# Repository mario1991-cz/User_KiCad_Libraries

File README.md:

# User KiCad Libraries

Personal KiCad 10 libraries (symbols, footprints, 3D models, SPICE models, design blocks).
Kept outside projects; all library-table entries use the path variable `${USER_LIB_DIR}`,
so the folder can be moved by changing that one variable. Kept in a Git repository (GitHub).

## Layout
| Folder | Content | Naming |
|---|---|---|
| `symbols/` | `.kicad_sym` libraries | `User_<Category>.kicad_sym` |
| `footprints/` | `.pretty` libraries | `User_<Category>.pretty` |
| `3dmodels/` | `.3dshapes` folders, STEP only | `User_<Category>.3dshapes` (same category as the footprint library) |
| `spice/` | SPICE models (`.lib`, `.mod`, `.sub`) | manufacturer or part family name |
| `design_blocks/` | `.kicad_blocks` libraries | `User_<Category>.kicad_blocks` |

Categories follow the official KiCad library names (`Regulator_Switching`, `Amplifier_Operational`,
`Connector`, `74xx`, ...). A library is created when its first part is added, never empty.

## Rules
- Use an official KiCad symbol/footprint whenever one exists. Add a part here only if KiCad lacks it
  or it needs a deliberate deviation.
- Prefer KiCad's official footprints in own symbols; own footprints only when KiCad has none.
- Symbols follow KiCad KLC style: 2.54 mm pin grid, inputs left, outputs right, power top/bottom,
  IEC (European) graphic conventions.
- Mandatory symbol fields: Reference, Value, Footprint, Datasheet (manufacturer PDF URL),
  Description, Keywords (`ki_keywords`), Footprint filters (`ki_fp_filters`).
- `Sim.*` fields (Sim.Library, Sim.Name, Sim.Device, Sim.Pins) are filled whenever a SPICE model is
  available; `Sim.Library` uses `${USER_LIB_DIR}/spice/<file>`. Models need ngspice with XSPICE
  (KiCad's ngspice has it).
- Models whose licence forbids redistribution (e.g. Central Semiconductor 2N5551) are not stored here:
  the symbol uses `Sim.Library = ${KIPRJMOD}/spice/<file>` and each project keeps its own copy of the model.
- Every new model is checked in ngspice before it is linked; LTspice-only syntax (`mfg=`, `Vceo=`, `Icrating=`,
  Diotec-style parametrised subcircuits) makes ngspice abort.
- No Manufacturer / MPN fields; vendor/SnapEDA extra fields (MF, MP, Price, Availability, PARTREV, ...) are removed.
- Names of own parts stay short and readable (original vendor names), KiCad naming conventions are not enforced.
- Connector pins are `passive` (power source pins only on real sources such as regulator/converter outputs).
- References in designs always end with a number (KiCad refuses to simulate `Rz` etc.).
- All texts, names and comments in English.

## User_74xx_CSN and User_4xxx_CSN – unofficial, obsolete symbol style
> **Warning:** `User_74xx_CSN` and `User_4xxx_CSN` are **unofficial** libraries. Its symbols follow the classic Czechoslovak
> ČSN drawing style known from TESLA catalogues. That standard is **withdrawn** and has been replaced by
> ČSN EN 60617-12 (IEC 60617-12). The library is kept for hobby and retro (TESLA) projects only; do not use it
> where conformity with current standards is required.
- Simple gates look the same in both standards (rectangle with `&`, `≥1`, `1`, `=1`, negation circle).
- Flip-flops, counters, decoders etc. are drawn in the classic style (TESLA catalogue), not with IEC dependency notation.
- One unit per gate/element plus a separate power unit (VCC/GND); Footprint field left empty, footprint filters for DIP/SOIC/TSSOP.
- Keywords contain the TESLA equivalent (e.g. `MH7400`) for searching.
- Layout of complex parts: three columns (input labels | function abbreviation | output labels); groups separated by
  lines, group headers such as `&G`, `&L`, `A`, `Z` (3-state outputs). Abbreviations as in TESLA catalogues:
  `T` flip-flop, `TE` edge register, `TL`/`RGL` latch, `RG8` shift register, `CT2`/`CT10` counter,
  `B/D`, `B/DEC`, `DC`, `X/Y` decoders, `MUX`/`MX` multiplexer, `SM` adder.
- Clock inputs: filled arrow. Tip at the body = rising edge (`C_H`); tip pointing away from the body
  towards the pin = falling edge (`C_L`, e.g. 74112). Negation = circle.
- Parts without a TESLA catalogue drawing (e.g. 74161, 74163, 74191, 74165, 74595) are drawn from their function in the same style.
- Generated by local scripts (not in the repository).
- 4000 series: supply pins VDD/VSS (4051/4052/4053 also VEE in the power unit); analog switch/multiplexer channels are `passive` pins; keywords contain the TESLA name (e.g. `MHB4011`).

## Design blocks
- A block contains only footprints, tracks and vias (plus the schematic). **No zones/copper pours and no Edge.Cuts outline**:
  pours are a board-level decision and the target board's planes connect the nets.
- Every GND pad gets its own short trace + via, so GND connects to the target board's plane on any layer
  (a 2-layer target without any GND pour would show these vias as unconnected in DRC).
- Pours and a temporary outline may be used in the block's work project only, to verify connectivity with DRC.
- A block has no required shape; in KiCad it is just a group.
- Usage in the PCB editor: **place the design block first, then run "Update PCB from Schematic"**.
  Updating first brings the block's parts in as loose footprints without the layout.
- Placed blocks are not updated when the library block changes.

## Tools
Helper scripts (3D model generators, symbol generators, mechanical drawing) are kept locally in `tools/`
and are deliberately **not part of this repository** (`.gitignore`). Models and symbols made with them are
ordinary KiCad/STEP files and need no script.

## Candidates (add when needed)
- 4000 series: 4020, 4024 (binary counters), 4026, 4033 (decade counter + 7-segment decoder), 4510, 4516 (up/down counters),
  4514, 4515 (1-of-16 decoder with latch), 4067 (16-channel analog mux), 4099 (8-bit addressable latch; TESLA drawing exists),
  4042 (quad D latch), 4543 (BCD to 7-segment LCD decoder), 4098 (dual monostable).
- 74HC40xx parts (74HC4051/4052/4053/4060/4040/4017 …) are pin-compatible with the 4000 originals: use the User_4xxx_CSN
  symbol and change Value (mind the 2–6 V supply range of HC).

## Contents
| Library | Part | Notes |
|---|---|---|
| `User_Regulator_Switching` (symbol) | TPS5405DR | TI 6.5–28 V in, 5 V fixed out, 2 A buck, SOIC-8, uses KiCad footprint `Package_SO:SOIC-8_3.9x4.9mm_P1.27mm`. No SPICE model from TI. |
| `User_Power` (design block) | TPS5405_5V_2A | Proven 5 V / 2 A supply from project PNAE (schematic) with a new 2-layer PCB layout (DRC clean). GND zones removed 2026-10-24 – only footprints, tracks and per-pad GND vias. |
| `User_Connector` (symbol + footprint + 3D) | RASPBERRYPI_B+_IDC / AMPHENOL_75869-107LF | Raspberry Pi 40-pin GPIO header with signal names (Adafruit symbol), shrouded 2x20 box header; pad 1 square. |
| `User_Connector` (symbol + footprint + 3D) | PJ-047A / CUI_PJ-047A | Same Sky (CUI) DC jack, 2.0 mm pin, 2.5 A, THT; all pins passive, shield pins unified as SHIELD. |
| `User_Connector` (symbol + footprint + 3D) | RCJ-04x / CUI_RCJ-04x | Same Sky (CUI) RCJ-04x RCA jack, right angle, THT (x = housing colour, 1 black ... 7 orange); pin 2 = centre (signal), pin 1 = sleeve (GND). Board-edge part: front face of the body at x = -4 mm = board edge; the two locating notches (1.7 × 1.8 mm, open to the edge) are drawn on Edge.Cuts inside the footprint and are milled with the outline (join the board outline to their end points). 3D model Same_Sky_RCJ-041.step (rotation/offset to be checked in the 3D viewer). |
| `User_Connector` | HTST-117-01-L-DV-A | Samtec shrouded header 2×17, 2.54 mm, SMD vertical, alignment pins (-A). Symbol = KiCad `Connector_Generic:Conn_02x17_Odd_Even` with fields filled, ref J, passive pins. Footprint `SAMTEC_HTST-117-01-L-DV-A` per Samtec HTST-SM rev D: pads 1.27 × 5.08 mm at ±3.43 mm, 2× NPTH Ø1.676 at ±19.05 mm, origin = connector centre, pin 1 bottom left (odd row at +Y), as `AMPHENOL_75869-107LF`. 3D = Samtec/TraceParts STEP rotated into KiCad axes by rewriting its points/directions (X→−X, Z→Y, Y+1.27→Z), so the footprint needs no rotation/offset. |
| `User_Converter_DCDC` (symbol + footprint + 3D) | TMR 9-2423WI / CONV_TMR_9-2423 | TRACO 9 W isolated DC/DC, 9-36 V in, +/-15 V 300 mA, SIP-8; pinout and footprint checked against the TMR 9WI datasheet. |
| `User_Transistor_FET` (symbol) | BUZ71 | 50 V / 14 A / 0.1 Ω N-channel MOSFET, TO-220 (pins 1 G, 2 D, 3 S; tab = drain). Graphics copied from KiCad `Transistor_FET:BUZ11`, footprint `Package_TO_SOT_THT:TO-220-3_Vertical`. |
| `User_Display_Character` (symbols) + `User_Display_7Segment` (footprint + 3D) | SA08-11GWA, SA08-11EWA, SA08-11SRWA, SA08-11YWA / SA08-11xxx | Kingbright 20.32 mm (0.8") single-digit 7-segment display, common anode, right-hand decimal. Colour variants are derived symbols of SA08-11GWA (graphics from KiCad `Display_Character:SA15-11SRWA`); pins A1 B14 C12 D10 E4 F2 G13 DP9, CA 3/5/11/16 (all four shown), pin 6 = hidden NC (no chip); pins 7, 8, 15 do not exist. Footprint `SA08-11xxx`: 13 pads 1.6 mm / drill 0.8 mm for the 0.5 mm pins (hand soldering; the datasheet's 1.0 mm lets too much solder through), pad 1 square. 3D model generated by a local script (the public model has 16 pins, no colours and 2.6 MB). Datasheet: keep the body ≥ 5 mm from the board edge for wave soldering. |
| `User_Mechanical` (symbol) + `User_Heatsink` (footprint + 3D) | V4330N | Assmann WSW V4330N heatsink for a TO-220 lying between the fins (29 × 20 × 11.5 mm, 12 K/W). Separate mechanical part (ref HS, graphics from KiCad `Mechanical:Heatsink`), footprint without pads, **origin = centre of the M3 hole** – drag it onto the transistor's hole, KiCad snaps it. The hole itself belongs to the transistor footprint. STEP = TraceParts model moved so the hole is at the origin. |
| `User_Heatsink` (footprint + 3D) | V4330N_Vertical | Alternative upright mounting of the V4330N (stands on its 29 × 11.5 mm end, 20 mm high): TO-220 tab on the inner face of the base between the fins; 2× NPTH Ø3.0 for self-tapping screws into the profile grooves, pitch 24 mm, 1.25 mm behind the lead axis. **Origin = pin 1 of the transistor** – drag it onto pad 1, KiCad snaps it. STEP = the V4330N model rotated upright in the file (hole 17 mm above the board). |
| `User_Package_TO_SOT_THT` (footprint) | TO-220-3_Vertical_A2.5mm_Z1mm, TO-220-2_Vertical_A2.5mm_Z1mm | KiCad TO-220 vertical footprints for V4330N_Vertical: pads unchanged, graphics with the tab back 2.5 mm behind the lead axis (datasheet A2 ≈ 2.5 mm; KiCad uses 3.15), KiCad 3D model with offset (0, −0.65, 1) so the tab sits on the heatsink and its hole is 17 mm above the board. |
| `User_Package_TO_SOT_THT` (footprint + 3D) | TO-220-3_Horizontal_TabDown_L20.32mm_Z2.5mm | TO-220 lying tab down on a heatsink base 2.5 mm above the board, leads bent 20.32 mm from the M3 hole (Ø3.2) axis; pads 1.905 × 2 / drill 1.1, origin pin 1. For V4330N and other heatsinks mounted the same way. |
| `User_Heatsink` (footprint + 3D) | HSS-B20-061H-03 | Same Sky (CUI) stamped TO-220 clip heatsink 19 × 12.7 × 13 mm with one solder pin (oval PTH; unused if a heatsink without pin is fitted). Geometry copied from KiCad `Heatsink:Heatsink_AAVID_576802B03900G` (practically identical), 3D model from Same Sky (`HSS-B20-061H-03.step`, rotation tuned by the user in Electronic_load). Use with symbol `Mechanical:Heatsink_Pad` or as a board-only footprint. |
| `User_Diode` (symbol) + `User_Diode_THT` (footprint + 3D) | SBX3040-3G | Diotec 40 V / 30 A Schottky rectifier, axial Ø8 × 7.5 mm (~P600, "D8x7.5_LowRth"), leads Ø1.6 mm. Symbol graphics from KiCad `Device:D_Schottky` (pin 1 K, 2 A). Footprint `SBX3040-3G`: horizontal, pitch 17.78 mm, pads 3.4 mm, drill 1.9 mm (production-proven; 1.8 mm soldered badly), pad 1 = K square. 3D model generated by a local script (bent leads, bend radius 1.6 mm). No SPICE model from Diotec. |
| `User_Potentiometer_THT` (footprint + 3D) | CA9PV10 | ACP CA9 10 mm trimmer, vertical, pins 2.5 × 5 mm apart. Geometry from KiCad `Potentiometer_THT:Potentiometer_ACP_CA9-V10_Vertical`, whose 3D model does not exist in KiCad. 3D model `CA9PV10.stp` from ACP, offset (17.99, -23.948, 5.8), rotate (0, 0, 90): checked in a KiCad STEP export, pins on pads and shoulder on the board. Height 6.1 mm above the board. |
| `User_Device` (symbol) | 3862C-162 | Bourns 3862 panel pot: graphics, pins and SPICE fields of KiCad `Device:R_Potentiometer` (1 = end, 2 = wiper, 3 = end), ref **P** (user convention), Value = resistance (default 10k), footprint preset `User_Potentiometer_Panel:3862C-162`, footprint filter `User_Potentiometer_Panel:*` (only panel pots offered). One symbol for all resistance values. |
| `User_Regulator_Switching` (symbol) + `User_Package_DIP` (footprint + 3D) | VIPER37LE / SDIP-10_W7.62mm_P1.778mm | ST VIPerPlus offline converter, 800 V, 60 kHz, SDIP10 (H = 115 kHz variant not added – user uses LE only). Symbol in the style of KiCad `VIPer26LN`: 1 GND, 2 VDD, 3 CONT, 4 FB, 5 BR, 6–10 DRAIN (7–10 stacked, hidden), ref U, footprint preset. Footprint: shrink DIP pitch 1.778 mm (70 mil), rows 7.62 mm, pads 1.78 × 1.27 mm, drill **0.6 mm – proven on the user's ViPer37LE board** (pins 0.36–0.56 mm fit), pad 1 square, origin pin 1, KiCad DIP-style silk/fab/courtyard. Heat-sink copper under DRAIN is drawn on the board (shape depends on the layout). 3D generated by a local script (KiCad has no SDIP10; the old workaround was the DIP-10 model scaled Y 0.7). |
| `User_Mechanical` (symbol) + `User_Heatsink` (footprint + 3D) + `User_Package_TO_SOT_THT` (footprint) | V2012B / TO-126-3_Vertical_Z4.1mm | Assmann WSW V2012B **clip-on** heatsink for TO-126 (black anodized, 22 × 11 × 19 mm, 21 K/W, sheet 0.8 mm), drawing ASS 0862 HS rev02. Separate mechanical part like V4330N: symbol ref HS (no pins), footprint origin = pin 1 of the transistor. The transistor slides **inside**, metal back on the inner face of the flat wall, top edge against the Ø1.5 dimple stop (the Ø3 hole is only for the alternative screw mounting, not used with the clip). Two solder pins, **not connected** (pads without number), in **slots 1.1 × 2.0 mm** (pad 2.2 × 3.1, annular ring 0.55 mm; less solder flowing through when hand soldering) at x −8.32 / 12.88, y +2.175 (pitch 21.2). The 3.2 mm wide pin shoulders keep the heatsink **3 mm above the board**. STEP from Assmann/TraceParts checked against the drawing (all dimensions match), rotated 180° about X in the file (representation frame left at identity) and coloured black. Transistor footprint `TO-126-3_Vertical_Z4.1mm` = KiCad TO-126-3_Vertical with the 3D model raised 4.1 mm (body top 18.1 mm above the board, just under the dimple at 18.15) and the Reference moved in front of the leads (pads unchanged). Checked by a kicad-cli STEP export: no overlap of transistor body and heatsink. |
| `User_Device` (symbol) + `User_Potentiometer_THT` (footprint + 3D) | PDB182-K | Bourns PDB18 17 mm dual-gang potentiometer, pin configuration K (PC pins down, shaft parallel to the board), M7 × 0.75 bushing, 6 mm shaft; one symbol/footprint for all PDB182-K… variants (detent, shaft length, taper, resistance – set Value). Symbol = KiCad `Device:R_Potentiometer_Dual_Separate` (units A/B, Sim fields kept), ref **P**, footprint preset, fp filter `User_Potentiometer_THT:PDB18*`. Footprint: origin = pin 1 of the front section, pads 1–3 front section R1, 4–6 rear section R2 (1'–3', row 5 mm behind), pitch 5 mm, pins 1.0 × 0.5 mm in **slots 1.3 × 0.8 mm**, pads 2.1 × 1.6 (annular 0.4), pad 1 rect; mounting face (panel) 3.8 mm in front of the front row (F.Fab dashed line "PANEL"), anti-rotation lug 2 mm at x +2.3…+3.4 (pin-1 side, axis height), shaft axis at x −5, 12.5 mm above the board. STEP = Bourns PDB182-K2220K (L 20 mm), turned into KiCad axes in the file (points (z − 5, x + 3.85, y + 12.5)), grey colour added; checked by a kicad-cli STEP export. |
| `User_Switch` (symbol) + `3dmodels/User_Switch.3dshapes` | A20405RNZQ | C&K (Littelfuse) A Series rotary switch A204: 2 poles × 4 positions (DP4T), 30° index, non-shorting, solder lugs, panel mount (3/8-32 bushing, 6.35 mm flatted shaft). Two units drawn like KiCad `SW_Rotary_1x4_MP` (MP pin removed): **unit A = pole A (common A, positions 1–4), unit B = pole C (common C, positions 7–10)** – terminal letters/numbers as moulded on the housing; drawn in position 1 (fully CCW). Ref SW, no footprint, **Exclude from board set by default** (wired panel part, stays in the BOM); an unused pole = simply do not place unit B. STEP from C&K (Pro/E, inches, coloured) stored unchanged for enclosure/front-panel models only (no footprint uses it). |
| `User_Connector` (symbol + footprint + 3D) | SJ1-3535 / CUI_SJ1-3535 | Same Sky (CUI) 3.5 mm stereo jack, right angle THT, threaded M6 × 0.5 bushing (panel nut), tip and ring switches. Symbol = KiCad `Connector_Audio:AudioJack3_SwitchTR` graphics with **pin numbers from the datasheet**: 1 sleeve, 2 tip, 3 ring, 4 tip switch, 5 ring switch; ref J, footprint preset, datasheet = Same Sky product page. Footprint from the datasheet's recommended layout (SJ1-353X, 09/12/2024): 5 slots 2.0 × 0.8 mm, pads 2.8 × 1.6 (annular 0.4), **pad 1 2.8 × 1.4** so that copper is 0.4 mm from the board edge with the body front flush with the edge (pin 1 is only 1.1 mm behind the front face); origin = pin 1, front face / panel line 1.1 mm in front (F.Fab "PANEL"), plug axis at x +0.9. STEP = Same Sky model turned into KiCad axes in the file (representation frame left at identity), body recoloured black, terminals silver. |
| `User_Connector` (symbol + footprint + 3D) | FC68405 / CLIFF_FC68405 | CLIFF FC68405 (PHS-10B) dual stacked RCA jack, right angle, THT, top white (A) / bottom red (B), common sleeve. Symbol drawn like the CLIFF FW6192 schematic (two contacts above each other, shared ground): pins **1 S (common), 2 B (bottom), 3 A (top)**, ref J. Footprint from the CLIFF drawing – note the drawing's "PC LAYOUT (PRINT SIDE)" is the **bottom (solder side) view**, and its 14.5 mm dimension of the post slots is edge to edge (centres 16.2 mm, as Same Sky RCJ-22): origin = pin 1 (front), pin 2 (3.25, 4), pin 3 (4.5, −4), holes 1.2 / pads 2.0, plastic snap-in posts in NPTH slots 3.0 × 1.7 at (0.5, ±8.1); housing front face at x = −7 = board edge (F.Fab "PCB edge"), sleeves protrude 7.8 mm, panel screw ear Ø2.4 at +y. CLIFF has no 3D model → STEP derived from the Same Sky RCJ-2211 model (identical geometry): assembly flattened into one part (body + two insulators), rotated into KiCad axes, recoloured (cream body, black front plate, white/red insulators, silver metal). |
| `User_Potentiometer_Panel` (footprint + 3D) | 3862C-162 | Bourns 3862 1/2 in panel potentiometer, terminal style C (solder lugs, wired), bushing 1/4 in, shaft 1/8 in × 11.81 mm. Use with KiCad symbol `Device:R_Potentiometer` (ref P); the value code in the part number (e.g. 3862C-162-103AL = 10 kΩ) goes to Value. **Pad-less mechanical footprint** for the 3D view and enclosure checks only: origin = shaft axis at the mounting face (panel plane), shaft to −Y, body behind the panel to y 12.37, lugs to y 16.95. Model: Bourns STEP, offset (0, −12.12, 6.25), rotate (−90, 0, 180) – body resting on the board; change the Z offset in a project copy for the real panel hole height. DRC gives "no pad found for pin 1–3" (schematic parity) – expected, the pot is wired to a terminal block / connector; exclude these 3 warnings in the DRC window once per project. STEP export: footprint type is "unspecified" – enable "include unspecified" (kicad-cli without `--no-unspecified`). |
| `User_Transistor_FET` (symbols) + `spice/ECX10N20.lib`, `spice/ECX10P20.lib` | ECX10N20-W6, ECX10P20-W6 | Exicon N/P lateral MOSFETs for audio power stages, 200 V / 8 A / 125 W, Vgss ±14 V (no gate protection – add G-S Zeners). Graphics of KiCad `Q_NMOS_GSD` / `Q_PMOS_GSD`, pins **1 G, 2 S, 3 D** (tab = source), footprint `Package_TO_SOT_THT:TO-247-3_Vertical`. Simulation ready: `Sim.Device=SUBCKT`, `Sim.Library=${USER_LIB_DIR}/spice/ECX1xx20.lib`, `Sim.Pins=1=2 2=3 3=1` (PEDC Level 1 models from 1999: node 1 D, 2 G, 3 S). `ECX10N20.lib` corrected 2026-11-13: Cgd diode `MDD` grading coefficient M=1 → 0.99 – with M=1 the ngspice transient analysis aborts at t = 0 (division by zero in the junction charge); `ECX10P20.lib` is unchanged. |
| `User_Transistor_BJT` (symbols) + `spice/` models | 2N5551, MJE340, MJE350, BC546, BD139 | Bipolar transistors with SPICE fields (all models checked in ngspice 45.2). 2N5551 (TO-92, 1 E 2 B 3 C – not in KiCad as THT), MJE340/MJE350 (TO-126, 1 E 2 C 3 B – not in KiCad), BC546 and BD139 = copies of the KiCad symbols with models. Graphics of KiCad `Q_NPN_EBC`, `Q_NPN_ECB`, `Q_PNP_ECB`, `Q_NPN_CBE` (flattened). Models: MJE340/MJE350 onsemi (`MJE340.LIB`, `MJE350.LIB`, MODPEX 2004); BC546 → `BC546B.lib` (Philips 1991); BD139 → `BD139.LIB` (Fairchild, LTspice info parameters removed – the onsemi MODPEX BD139 gives Vbe ≈ 0.33 V and is not used). **2N5551: Central Semiconductor model must not be redistributed → not in this library; the symbol points to `${KIPRJMOD}/spice/2N5551.lib`, copy the model into each project.** |
| `User_Transistor_FET` (symbol) | IRLB4030PBF | Infineon 100 V / 180 A logic-level N-channel HEXFET, RDS(on) 4.3 mΩ max at 10 V, TO-220AB (pins 1 G, 2 D, 3 S; tab = drain). Graphics as BUZ71, footprint `Package_TO_SOT_THT:TO-220-3_Vertical`. SPICE: Infineon model (Symmetry MODPEX Level 1, checked in ngspice 45.2: RDS(on) 3.2 mΩ at 10 V, Vth 2.39 V). **The model header restricts commercial use (Symmetry licence) → not in this library; the symbol points to `${KIPRJMOD}/spice/IRLB4030.lib`, copy the model into each project** (`Sim.Pins=1=2 2=1 3=3`, subckt nodes 1 D, 2 G, 3 S). |
| `User_Isolator` (symbol) + `User_Package_SO` (footprint + 3D) + `spice/VOM1271.lib` | VOM1271 / Vishay_SOP-4_4.57x4.42mm_P2.54mm | Vishay photovoltaic MOSFET driver with integrated fast turn-off (Voc 8.4 V typ / 7.8 V min, Isc 15 µA at IF 10 mA; ton 53 µs, toff 65 µs), SOP-4: 1 LED anode, 2 LED cathode, 3 PV−, 4 PV+. Own symbol (KiCad has no PV driver), ref U. Footprint = Vishay recommended land pattern (pads 1.15 × 0.9 mm, 5.1 mm inner / 7.4 mm outer, pitch 2.54; KiCad's SOP-4/SO-4 footprints are drawn for other packages), filled silk triangle at pin 1. STEP from Vishay turned into KiCad axes in the file. SPICE model converted from LTspice: `n=13` series PV diodes replaced by one equivalent diode, pins +Iout/−Iout renamed IOP/ION, `.backanno` removed; checked in ngspice against the datasheet (Voc, Isc, toff). |
| `User_Switch` (symbol) + `User_Package_TO_SOT_THT` (footprint) | 67L075 / TO-220-2_Vertical_A2.79mm | Sensata (Airpax) 6700 bimetal disc thermostat, SPST normally closed, opens on rise at 75 °C ±5 °C, 0.5 A 48 VDC / 1 A 120 VAC, nickel-plated copper bracket (TO-220 outline, 2 leads at 5.08 mm), for mounting on a heatsink. Symbol = IEC 60617 S00265 (self-operating thermal switch, break contact), pins 1 top / 2 bottom, ref SW; simulation model = closed contact 50 mΩ (Sim.Device R). Footprint = KiCad TO-220-2_Vertical pads with the **bracket back face 2.79 mm behind the lead axis** (Sensata drawing; KiCad uses 3.15) so it sits flat on the heatsink like the A2.5mm variants; body 10.16 × 4.70 mm; KiCad 3D model with offset (0, −0.36, 0). |
| `spice/TL08x.lib` (model) | TL081, TL084, TL084_QUAD | TI/PSpice Boyle macromodels; TL084_QUAD maps all 14 pins of the quad symbol. |
| `User_74xx_CSN` (symbols) | Gates: 7400, 7402, 7403, 7404, 7408, 7410, 7411, 7414, 7420, 7421, 7427, 7430, 7432, 7486, 74132, 74HC4002. Flip-flops/latches/registers: 7472, 7474, 74112, 7475, 74174, 74175, 74273, 74373, 74374, 74573, 74574. Counters: 7490, 7493, 74192, 74193. Decoders/multiplexers: 7442, 7447, 74138, 74154, 74151, 74153, 74157. Shift registers: 74164, 74165, 74595. Buffers/transceivers: 74125, 74126, 74244, 74245. Other: 7483, 7485, 74123. Counters (drawn from function): 74161, 74163, 74191. | Classic ČSN / TESLA style (unofficial, see warning above). 7447 drawn after the GDR D147 (TESLA made no 7447). |
| `User_4xxx_CSN` (symbols) | Gates: 4001, 4011, 4012, 4023, 4025, 4069, 4070, 4071, 4077, 4081, 4093, 40106, 4049, 4050. Flip-flops/latches: 4013, 4027, 4043. Counters: 4017, 4029, 4040, 4060, 4518, 4520. Decoders: 4028, 4511. Analog: 4066, 4051, 4052, 4053. Shift registers: 4015, 4021, 4094. Other: 4046 (PLL), 4538 (monostable). | Classic ČSN / TESLA style (unofficial). 4050, 4051, 4053, 4066, 4081, 4518 after TESLA MHB catalogue drawings, the rest drawn from function. |

## Heatsinks and DRC
A heatsink is a separate part (HS*) placed over its transistor or regulator, so the courtyards overlap and the mounting hole lies inside the heatsink courtyard. The project templates (JLC_2L, JLC_4L, TSM_2L) contain a custom rule `Heatsink courtyard` that ignores exactly these two checks between HS* and Q*/U*/D*; any other part overlapping a heatsink is still reported. For older projects copy the rule into the project's `.kicad_dru`.

The former combined footprint `User_Heatsink:TO-220-3_Horizontal_V4330N` (transistor + heatsink in one) was moved into the H-bridge project library (2026-11-08) and is no longer part of this library.

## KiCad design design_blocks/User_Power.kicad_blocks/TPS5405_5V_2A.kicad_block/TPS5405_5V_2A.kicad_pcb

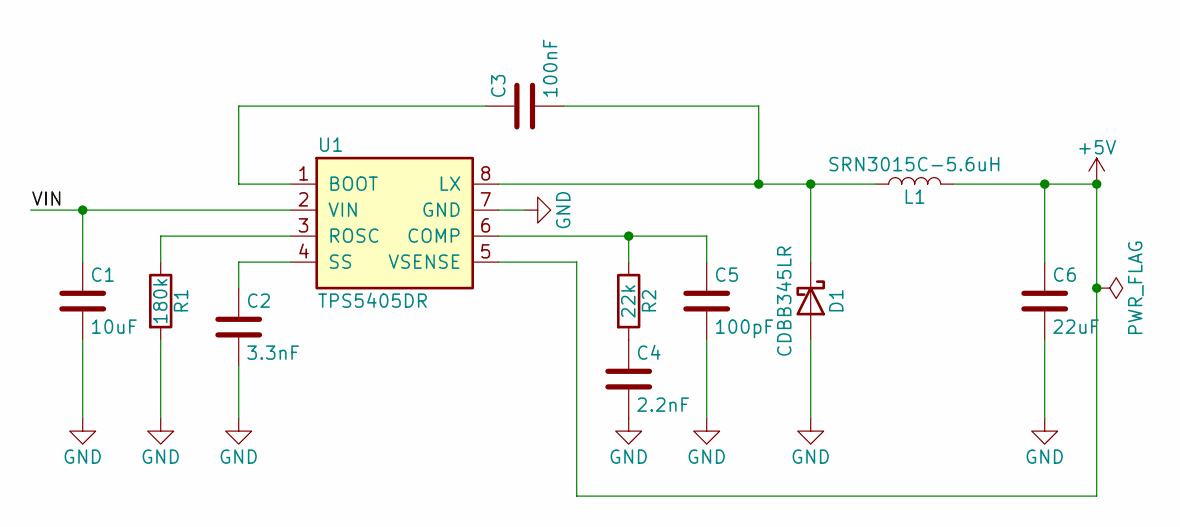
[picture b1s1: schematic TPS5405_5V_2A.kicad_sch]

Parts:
C1: 10uF; C_1206_3216Metric_Pad1.33x1.80mm_HandSolder
C2: 3.3nF; C_0805_2012Metric_Pad1.18x1.45mm_HandSolder
C3: 100nF; C_1206_3216Metric_Pad1.33x1.80mm_HandSolder
C4: 2.2nF; C_0805_2012Metric_Pad1.18x1.45mm_HandSolder
C5: 100pF; C_0805_2012Metric_Pad1.18x1.45mm_HandSolder
C6: 22uF; C_1206_3216Metric_Pad1.33x1.80mm_HandSolder
D1: CDBB345LR; D_SMB_Handsoldering
L1: SRN3015C-5.6uH; L_Cenker_CKCS3015
R1: 180k; R_1206_3216Metric_Pad1.30x1.75mm_HandSolder
R2: 22k; R_0805_2012Metric_Pad1.20x1.40mm_HandSolder
U1: TPS5405DR; SOIC-8_3.9x4.9mm_P1.27mm

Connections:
+5V: C6.1, L1.2, U1.5 (VSENSE)
/VIN: C1.1, U1.2 (VIN)
GND: C1.2, C2.2, C4.2, C5.2, C6.2, D1.2 (A), R1.2, U1.7 (GND)
unnamed: C4.1, R2.2
unnamed: C3.2, D1.1 (K), L1.1, U1.8 (LX)
unnamed: C3.1, U1.1 (BOOT)
unnamed: C5.1, R2.1, U1.6 (COMP)
unnamed: R1.1, U1.3 (ROSC)
unnamed: C2.1, U1.4 (SS)

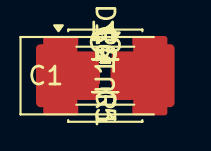
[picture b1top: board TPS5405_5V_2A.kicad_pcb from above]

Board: 2 copper layers, 11 parts (0 on the bottom side), 9 nets.
